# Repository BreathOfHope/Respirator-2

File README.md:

# Respirator-2

Respirator-2 takes the knowledge we gained in building the RespiratorApparatus to build a production ready version, that can be manufactured in an industrial setting. If a dire situation arises, this design can be used to mass produce respirators.

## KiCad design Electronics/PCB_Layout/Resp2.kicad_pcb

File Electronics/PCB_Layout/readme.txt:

Project and library files for KiCad based layout, in case you want to modify the layout, else use the gerber files direct.
Use the contents from pretty library for the footprints, some have custom properties.
The project (.pro) file has the reference to the schematics (.sch) and layout(.kicad_pcb) as well as the preferences.

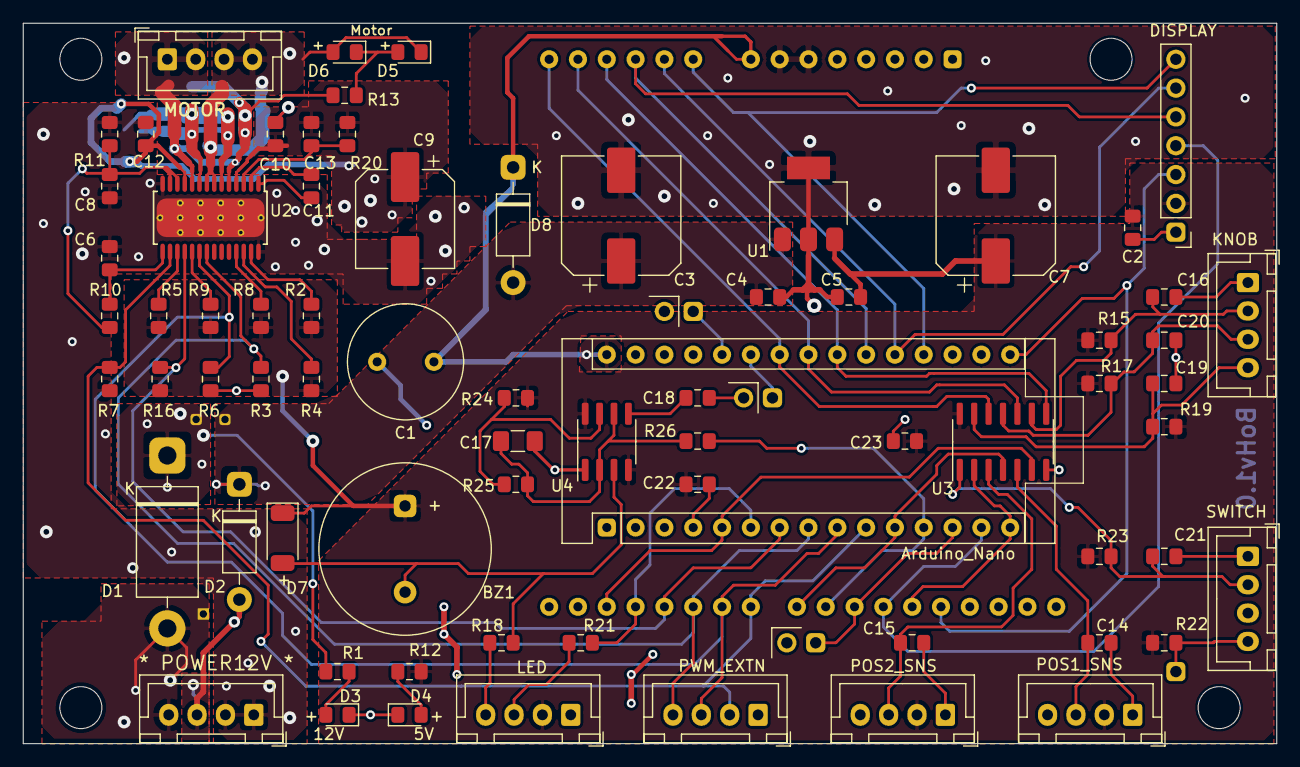
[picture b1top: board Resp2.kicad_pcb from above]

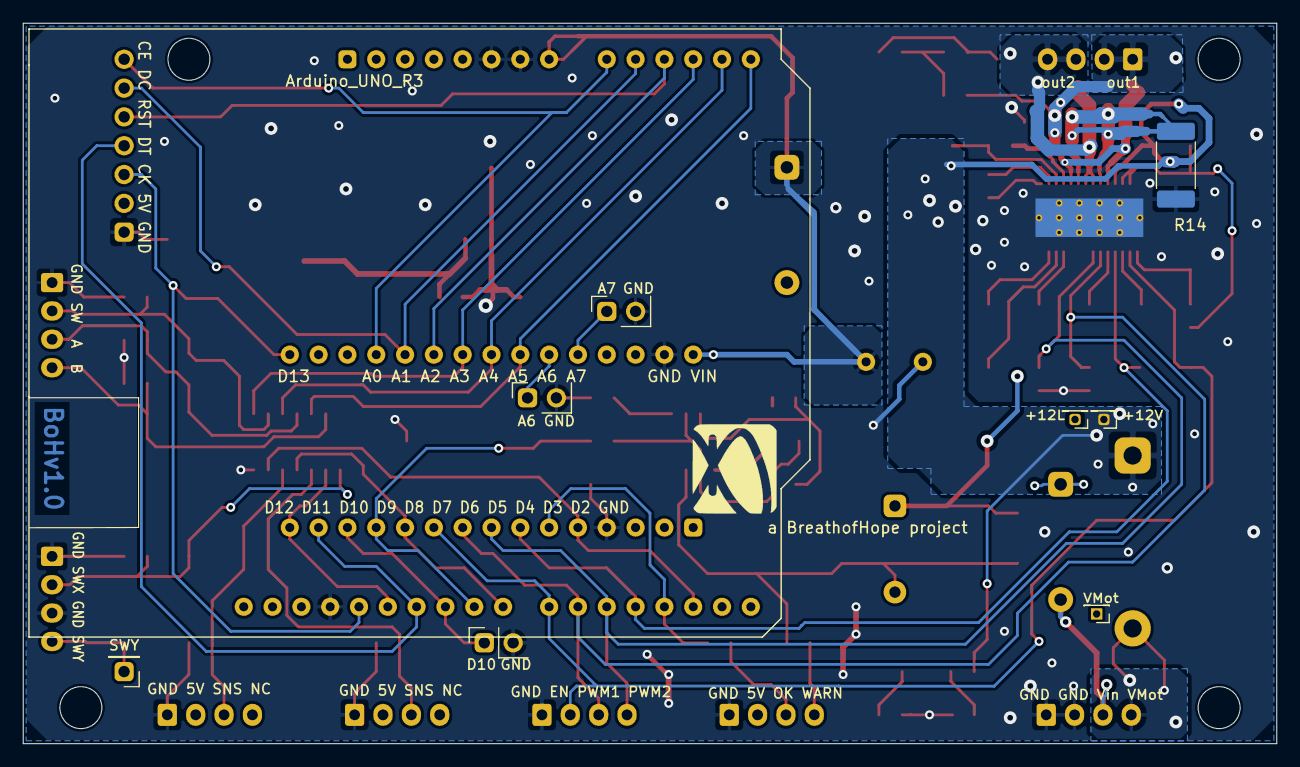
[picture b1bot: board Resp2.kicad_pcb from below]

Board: 2 copper layers, 110.5 x 63.5 mm, 84 parts (6 on the bottom side), 56 nets.

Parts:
A1: Arduino_Nano
A2: Arduino_UNO_R3
A6, A7: TP; PinHeader_1x02_P2.54mm_Vertical
BZ1: Buzzer; Buzzer_15x7.5RM7.6
C1: 1000uF 25V; C_Radial_D10.0mm_H20.0mm_P5.00mm
C2, C4, C5, C8, C10, C12, C14, C15, C16, C18, C19, C20, C21, C22, C23: 100nF; C_0805_2012Metric_Pad1.15x1.40mm_HandSolder
C3: 100uF25V; CP_Elec_10x10
C6: 470nF; C_0805_2012Metric_Pad1.15x1.40mm_HandSolder
C7: 100uF; CP_Elec_10x10
C9: 100uF25V; CP_Elec_8x10.5
C11: 10nF; C_0805_2012Metric_Pad1.15x1.40mm_HandSolder
C13: 100nF35V; C_0805_2012Metric_Pad1.15x1.40mm_HandSolder
C17: 10uF; C_1206_3216Metric_Pad1.42x1.75mm_HandSolder
D1: MUR460; D_DO-201AD_P15.24mm_Horizontal
D2, D8: 1N4001; D_DO-41_SOD81_P10.16mm_Horizontal
D3, D6: YLO; LED_0805_2012Metric_Pad1.15x1.40mm_HandSolder
D4, D5: RED; LED_0805_2012Metric_Pad1.15x1.40mm_HandSolder
D7: 1N4148W; D_SOD-128
D10: TP; PinHeader_1x02_P2.54mm_Vertical
H1, H2, H3, H4: MountingHole; MountingHole_3.7mm
J1: * POWER12V *; JST_XH_B4B-XH-A_1x04_P2.50mm_Vertical
J2: DISPLAY; PinHeader_1x07_P2.54mm_Vertical
J3: PWM_EXTN; JST_XH_B4B-XH-A_1x04_P2.50mm_Vertical
J4: MOTOR; JST_XH_B4B-XH-A_1x04_P2.50mm_Vertical
J5: POS1_SNS; JST_XH_B4B-XH-A_1x04_P2.50mm_Vertical
J6: POS2_SNS; JST_XH_B4B-XH-A_1x04_P2.50mm_Vertical
J7: KNOB; JST_XH_B4B-XH-A_1x04_P2.50mm_Vertical
J8: LED; JST_XH_B4B-XH-A_1x04_P2.50mm_Vertical
J9: SWITCH; JST_XH_B4B-XH-A_1x04_P2.50mm_Vertical
R1, R10, R13, R15, R16, R17, R19, R22, R23: 10k; R_0805_2012Metric_Pad1.15x1.40mm_HandSolder
R2, R4, R5, R7, R8, R9: 4k7; R_0805_2012Metric_Pad1.15x1.40mm_HandSolder
R3, R6: NM4k7; R_0805_2012Metric_Pad1.15x1.40mm_HandSolder
R11, R12: 2k2; R_0805_2012Metric_Pad1.15x1.40mm_HandSolder
R14: 0R022; R_2512_6332Metric_Pad1.52x3.35mm_HandSolder
R18, R21, R26: 1k; R_0805_2012Metric_Pad1.15x1.40mm_HandSolder
R20: 1M; R_0805_2012Metric_Pad1.15x1.40mm_HandSolder
R24, R25: 470k; R_0805_2012Metric_Pad1.15x1.40mm_HandSolder
TP1: VMot; PinHeader_1x01_P1.27mm_Vertical
TP2: +12V; PinHeader_1x01_P1.27mm_Vertical
TP3: +12L; PinHeader_1x01_P1.27mm_Vertical
TP4: SWY; PinHeader_1x01_P2.54mm_Vertical
U1: LM2937xMP; SOT-223-3_TabPin2
U2: DRV8842PWP; HTSSOP-28-1EP_4.4x9.7mm_P0.65mm_EP3.4x9.5mm_ThermalVias
U3: 74HC14; SOIC-14_3.9x8.7mm_P1.27mm
U4: NE555; SOIC-8_3.9x4.9mm_P1.27mm

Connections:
+5V: BZ1.1, C2.1, C5.1, C7.1, C22.1, C23.1, D7.1, J2.2, J5.2, J6.2, J8.2, R2.2, R4.2, R5.2, R8.2, R9.2, R12.1, R15.1, R16.1, R17.1, R19.1, R22.1, R23.1, R24.1, U1.3, U3.14, U4.4, U4.8
+12L: C3.1, C4.1, D2.1, D8.2, TP3.1, U1.1
+12P: D1.2, J1.4, TP1.1
+12V: C9.1, C10.1, C12.1, C13.1, D1.1, R1.1, R20.1, TP2.1, U2.4, U2.11
/Arduino_EncoderA: A1.23, A2.13, U3.10
/Arduino_EncoderB: A1.24, A2.14, U3.12
/Arduino_LCD_CE: A1.19, A2.9, J2.7
/Arduino_LCD_DC: A1.20, A2.10, J2.6
/Arduino_LCD_RST: A1.21, A2.11, J2.5
/Arduino_Rotary_switch: A1.22, A2.12, U3.8
/Arduino_Vin: A1.30, A2.8, C1.1, D8.1
/Arduino_buz_mute: A1.12, A2.24, R26.1
/Arduino_free_pin: A1.13, A2.25, D10.1
/Arduino_motor_ctrl1: A1.9, A2.21, J3.3, R6.1, U2.20
/Arduino_motor_ctrl2: A1.8, A2.20, J3.4, R3.1, U2.21
/Arduino_motor_fault: A1.7, A2.19, R16.2, U2.18
/Arduino_motor_reset: A1.10, A2.22, J3.2, R7.1, U2.16
/Arduino_ok_led: A1.6, A2.18, R21.2
/Arduino_posn_sns1: A1.5, A2.17, U3.6
/Arduino_posn_sns2: A1.11, A2.23, U3.4
/Arduino_switchX: A1.15, A2.27, U3.2
/SPI_CLK: A1.16, A2.28, J2.3
/SPI_MOSI: A1.14, A2.26, J2.4
/WarnLED: BZ1.2, D7.2, R18.2, U4.3
/out1: J4.1, J4.2, R13.1, U2.5, U2.10
/out2: D5.1, D6.2, J4.3, J4.4, U2.7, U2.8
GND: A1.4, A1.29, A2.6, A2.7, A2.29, A6.2, A7.2, C1.2, C2.2, C3.2, C4.2, C5.2, C6.2, C7.2, C8.2, C9.2, C10.2, C12.2, C14.2, C15.2, C16.2, C17.2, C18.2, C19.2, C20.2, C21.2, C22.2, C23.2, D3.1, D4.1, D10.2, J1.1, J1.2, J2.1, J3.1, J5.1, J6.1, J7.1, J8.1, J9.1, J9.3, R3.2, R6.2, R7.2, R11.2, R14.1, U1.2, U2.14, U2.28, U2.29, U3.7, U4.1
unnamed: A1.25, A6.1
unnamed: A1.26, A7.1
unnamed: C6.1, R10.1, U2.15
unnamed: C8.1, R10.2, R11.1, U2.12, U2.13
unnamed: C11.1, U2.2
unnamed: C11.2, U2.1
unnamed: C13.2, R20.2, U2.3
unnamed: C14.1, J5.3, U3.5
unnamed: C15.1, J6.3, U3.3
unnamed: C16.1, J7.2, R15.2, U3.9
unnamed: C17.1, R25.2, R26.2, U4.2, U4.6
unnamed: C18.1, U4.5
unnamed: C19.1, J7.4, R19.2, U3.13
unnamed: C20.1, J7.3, R17.2, U3.11
unnamed: C21.1, J9.2, R23.2, U3.1
unnamed: D2.2, J1.3
unnamed: D3.2, R1.2
unnamed: D4.2, R12.2
unnamed: D5.2, D6.1, R13.2
unnamed: J8.3, R21.1
unnamed: J8.4, R18.1
unnamed: J9.4, R22.2, TP4.1
unnamed: R2.1, U2.27
unnamed: R4.1, U2.26
unnamed: R5.1, U2.17
unnamed: R8.1, U2.25
unnamed: R9.1, U2.19
unnamed: R14.2, U2.6, U2.9
unnamed: R24.2, R25.1, U4.7

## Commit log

2020-04-02 Add electronics greb and sch files
2020-04-02 Correct PDFs
2020-04-02 Correct folder name
2020-04-02 created readme for schematics
2020-04-02 created readme for gerber files
2020-04-03 This is the first set of drawings released to manufacturers. Includes parts that can be manufactured by turning and milling. Contributions from Vignesh Nagarajan, and the Respirator discussion group 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
2020-05-19 added electronics bom
2020-05-19 added drawings for mechanical components and mechanical bom
2020-05-19 updated readme for modifications needed with Nano
2020-05-19 updated readme on PCB wiring needed for Nano usage
2020-05-19 update readme for PCB changes
2020-05-20 updated assembly BoM
    updated device descriptions
2020-05-20 versionB schematics - KiCad and pdf files
    BoHv0.1(beta) PCB was fabricated and needed some wirings for using Nano and the interrupts were suboptimal. Hence the new version schematics and PCB files. Yet to fabricate the BoHv1.0 PCB.
    Updated Arduino connections for optimised interrupt usage.
    D2 used for position sense, D3 usable as extra source of interrupt
    Swapped Arduino Nano's A6-A7 pin connections with its unused A4-A5 pins.
2020-05-20 Moved v0.1 schematics to separate folder
2020-05-20 updated readme and moved v0.1 files to separate folder
2020-05-20 moved v0.1 gerber files to separate folder
2020-05-20 added v1.0 files and moved v0.1 gerber files to subfolder
    BoHv0.1 PCB was manufactured and validated, based on which the BoHv1.0 gerbers are now generated, yet to be manufactured.
    PCB layout done with KiCad, project file(s) to be included.
    The PCB enhancements include,
    - using A4-A5 pins on the nano connector instead of A6-A7.
    - using D2 (external interrupt) for position sensor instead of D7 (pin change interrupt.)
    - D10 available as a free pin for user connections
2020-05-20 renamed file for v0.1 PCB
2020-05-20 created directory for KiCad layout
2020-05-20 project and layout files for KiCad
2020-05-20 Created Resp2.pretty directory for footprints
2020-05-20 Added footprint files
2020-05-20 Added footprint file for every component on PCB
2020-05-20 moved BoM to a subdirectory
2020-05-20 Updated BoM for v1.0 PCB
2020-05-20 moved readme to v0.1 files
2020-05-20 updated readme about BoHv1.0
2020-05-21 BoM already in separate folder
2020-05-21 Updated gerber file
2020-05-21 renamed directory as PCB_Fabrication
2020-05-21 updated gerber renamed directory
2020-05-21 update file and renamed directory
2020-05-21 updated file and renamed directory
2020-05-21 updated file renamed folder
2020-05-21 updated file and renamed folder
2020-05-21 updated file and moved it to v0.1 directory
2020-05-21 updated readme for BoHv1_0 PCB
2020-05-21 renamed directory
2020-05-21 Rename Electronics/gerber/v0.1/BoHv0_1.topsilk.gbr to Electronics/PCB_Fabrication/v0.1/BoHv0_1.topsilk.gbr
2020-05-21 added 3D views of the BoHv1_0 PCB
2020-05-30 uploaded breathof hope logo
    for use in silk screen
2020-05-30 updated layout file
2020-05-30 updated kicad project
2020-05-30 updated gerbers
    corrected min track to 10 mil
    added logo
2020-05-30 updated gerbers
    added logo
    increased min width and spacing to 10 mil
2020-05-30 updated gerbers
    Added logo
    increased spacing and min width to 10 mil
2020-05-30 updated gerbers
    added logo
    increased min width and spacing to 10mil
